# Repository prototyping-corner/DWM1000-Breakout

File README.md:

# DWM1000 Breakout
  
This breakout is for the Decawave DWM1000 module in a breadboard friendly form factor with onboard logic level converter and status LED's. The DWM1000 is an IEEE802.15.4-2011 UWB compliant wireless module capable of precision indoor positioning and high data rates, making it perfect for projects that require localization where GPS may not be available or suitable.  

**Features:**  
– Decawave DWM1000 for precision tracking  
– Breadboard friendly form-factor  
– Connect to your micro of choice  
– Operate over 1.65 - 5.5 volt range with built-in logic level converter  
– Resistors and solder bridge pads for setting SPI phase and polarities  
– Exposed pads for SFD and ROK LEDs  
  
Open source hardware licensed [under the CERN OHL v1.2](https://github.com/prototyping-corner/DWM1000-Breakout/blob/master/LICENSE)  
Documentation licensed under [Creative Commons Attribution-ShareAlike 4.0](https://creativecommons.org/licenses/by-sa/4.0/)

**More information:**  
– [Decawave DW1000 datasheet](https://www.decawave.com/sites/default/files/resources/dwm1000-datasheet-v1.3.pdf)  
– [Decawave Application Notes](https://www.decawave.com/application-notes/)  
  
Purchase from [Tindie]() (coming soon)  
Usage documentation coming soon

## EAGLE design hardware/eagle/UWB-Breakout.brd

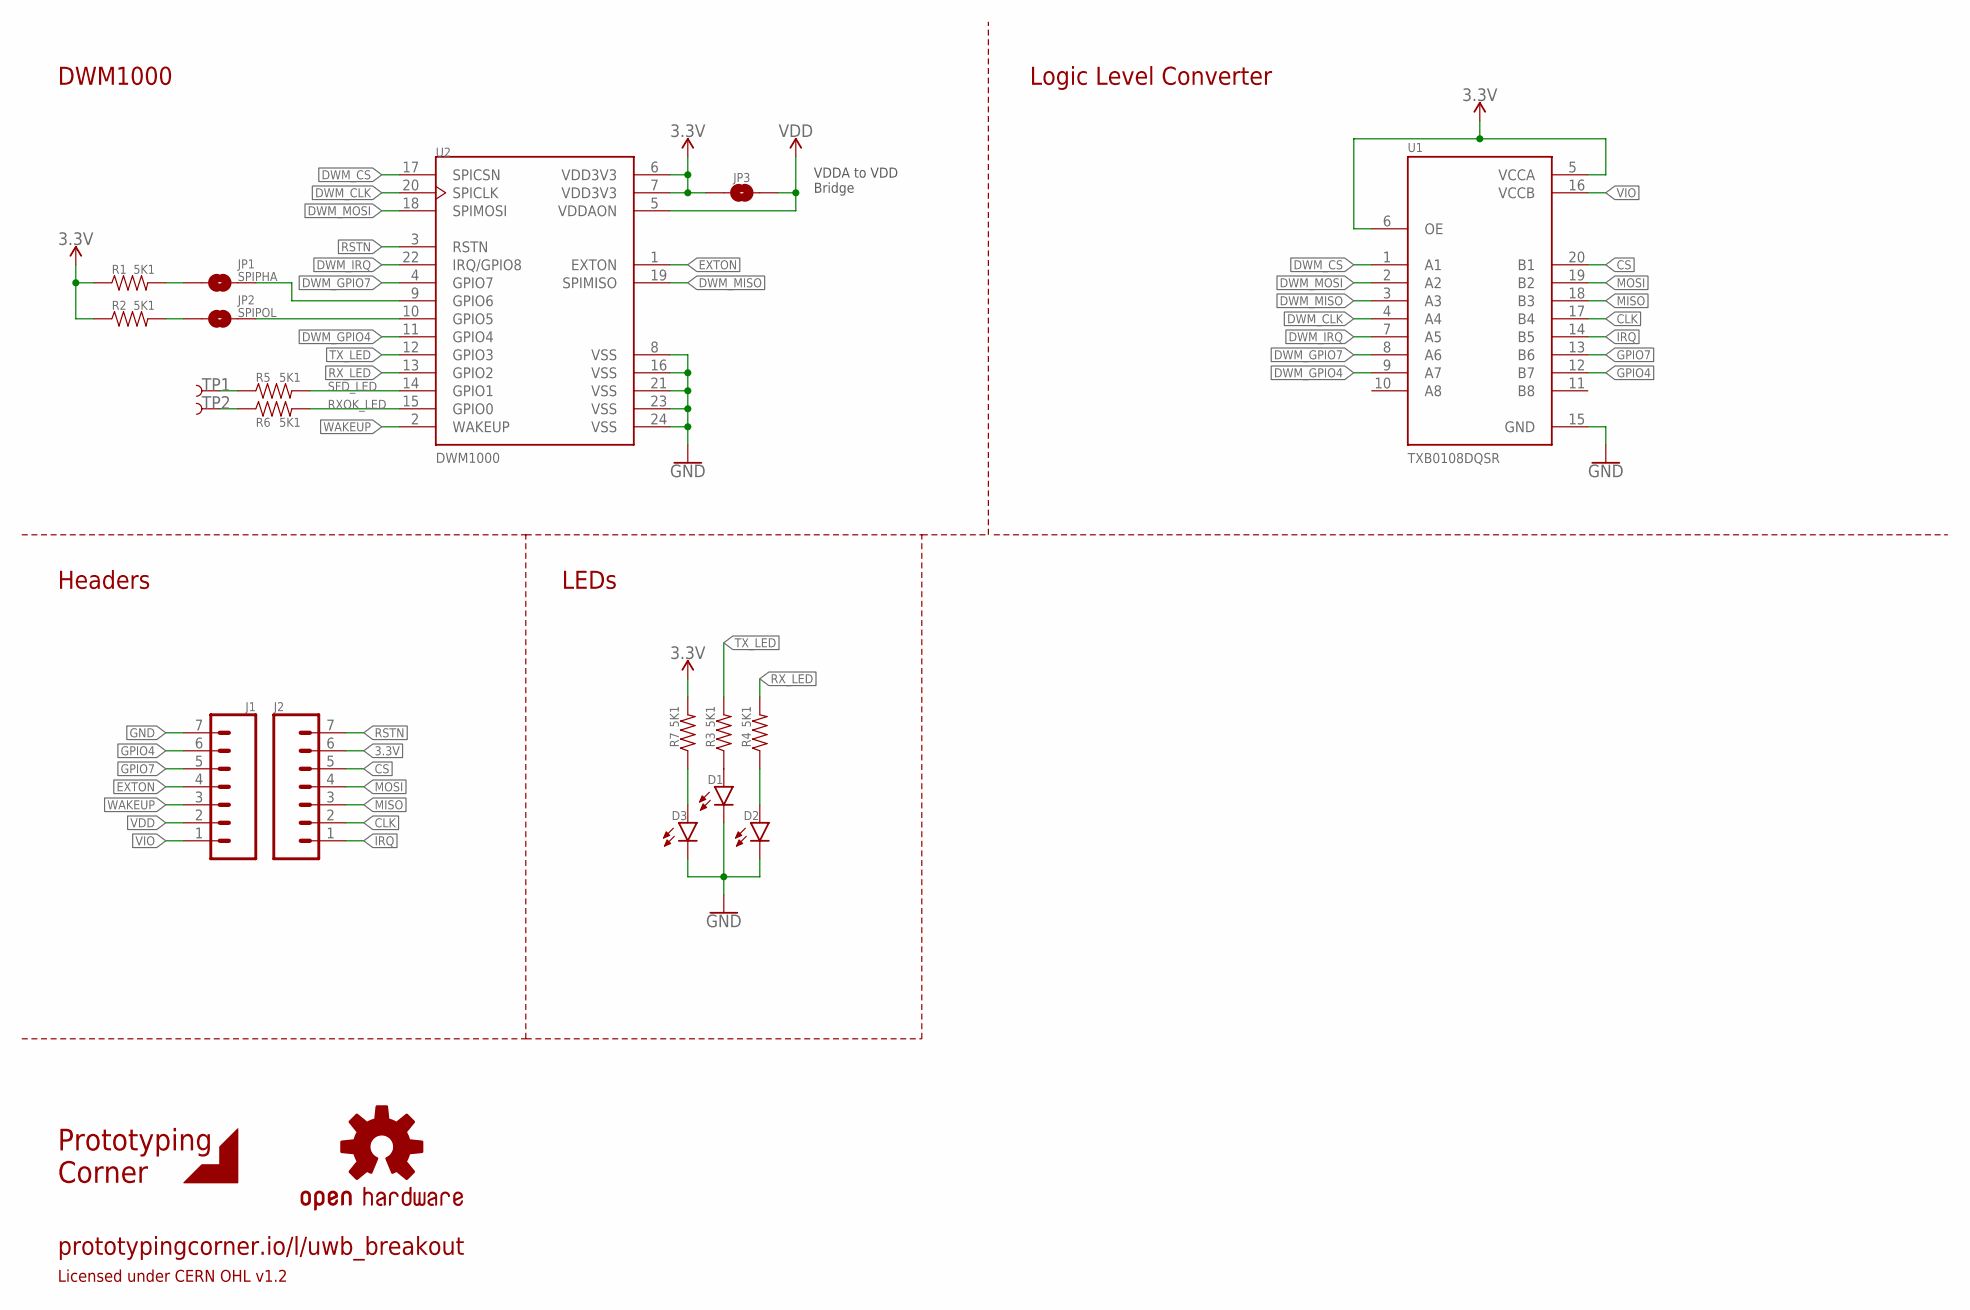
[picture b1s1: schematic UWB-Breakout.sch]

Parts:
D1: Yellow; LED-0603
D2: GREEN; LED-0603
D3: BLUE; LED-0603
J1, J2: CONN_07NO_SILK; 1X07_NO_SILK
JP1: SPIPHA; SMT-JUMPER_2_NO_SILK
JP2: SPIPOL; SMT-JUMPER_2_NO_SILK
JP3: JUMPER-SMT_2_NO_SILK; SMT-JUMPER_2_NO_SILK
LOGO1: OSHW-LOGOM; OSHW-LOGO-M
R1, R2, R3, R4, R5, R6, R7: 5K1; 0603
TP1, TP2: TEST-POINT3X5; PAD.03X.05
U1: TXB0108DQSR; SON40P400X200X55-20N
U2: DWM1000; XCVR_DWM1000

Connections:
3.3V: J2.6, JP3.1, R1.1, R2.1, R7.2, U1.5 (VCCA), U1.6 (OE), U2.6 (VDD3V3), U2.7 (VDD3V3)
CLK: J2.2, U1.17 (B4)
CS: J2.5, U1.20 (B1)
DWM_CLK: U1.4 (A4), U2.20 (SPICLK)
DWM_CS: U1.1 (A1), U2.17 (SPICSN)
DWM_GPIO4: U1.9 (A7), U2.11 (GPIO4)
DWM_GPIO7: U1.8 (A6), U2.4 (GPIO7)
DWM_IRQ: U1.7 (A5), U2.22 (IRQ/GPIO8)
DWM_MISO: U1.3 (A3), U2.19 (SPIMISO)
DWM_MOSI: U1.2 (A2), U2.18 (SPIMOSI)
EXTON: J1.4, U2.1 (EXTON)
GND: D1.C, D2.C, D3.C, J1.7, U1.15 (GND), U2.8 (VSS), U2.16 (VSS), U2.21 (VSS), U2.23 (VSS), U2.24 (VSS)
GPIO4: J1.6, U1.12 (B7)
GPIO7: J1.5, U1.13 (B6)
IRQ: J2.1, U1.14 (B5)
MISO: J2.3, U1.18 (B3)
MOSI: J2.4, U1.19 (B2)
unnamed: D3.A, R7.1
unnamed: D1.A, R3.1
unnamed: JP1.2, U2.9 (GPIO6)
unnamed: JP2.2, U2.10 (GPIO5)
unnamed: JP1.1, R1.2
unnamed: JP2.1, R2.2
unnamed: R6.1, TP2.P$1
unnamed: R5.1, TP1.P$1
unnamed: D2.A, R4.1
RSTN: J2.7, U2.3 (RSTN)
RXOK_LED: R6.2, U2.15 (GPIO0)
RX_LED: R4.2, U2.13 (GPIO2)
SFD_LED: R5.2, U2.14 (GPIO1)
TX_LED: R3.2, U2.12 (GPIO3)
VDD: J1.2, JP3.2, U2.5 (VDDAON)
VIO: J1.1, U1.16 (VCCB)
WAKEUP: J1.3, U2.2 (WAKEUP)

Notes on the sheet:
Prototyping Corner
prototypingcorner.io/l/uwb_breakout
Licensed under CERN OHL v1.2
VDDA to VDD Bridge
Headers
DWM1000
Logic Level Converter
LEDs

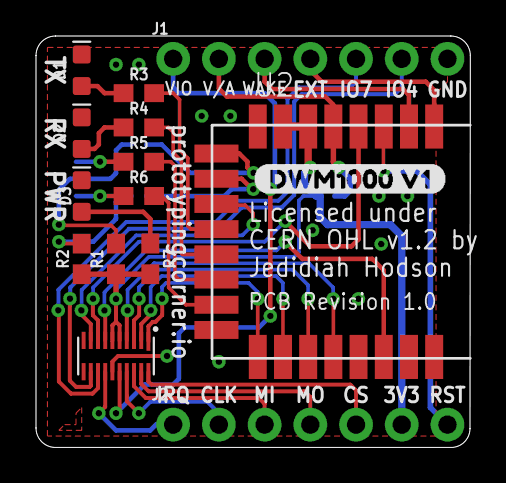
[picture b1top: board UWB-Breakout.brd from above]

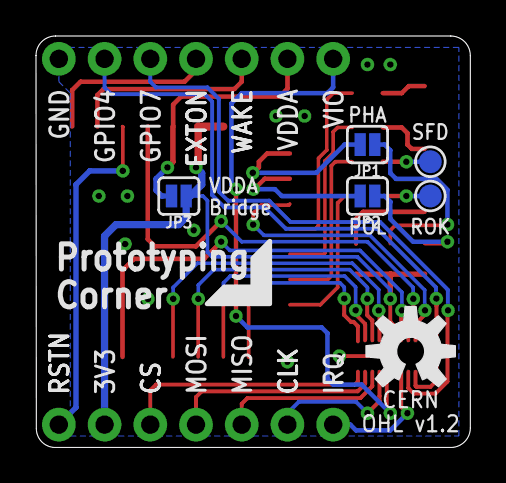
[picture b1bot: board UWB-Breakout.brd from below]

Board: 2 copper layers, 24.1 x 22.9 mm, 21 parts (6 on the bottom side), 34 nets.

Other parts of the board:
U$1: DWM1000_V10

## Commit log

2020-06-07 Added CERN OHL v1.2 license
2020-06-07 repo init
2020-06-07 Hardware V1 files

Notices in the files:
README.md:
License: CERN
hardware/eagle/UWB-Breakout.brd:
CERN OHL v1.2 by
Jedidiah Hodson
parts and their libraries:
SparkFun-LED: Licensing: Creative Commons ShareAlike 4.0 International - https://creativecommons.org/licenses/by-sa/4.0
